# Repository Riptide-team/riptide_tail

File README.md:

# Compilation

## Arduino makefile

To compile and upload the code on the Arduino, [Arduino-Makefile](https://github.com/sudar/Arduino-Makefile) is used. Once installed, go to src, check that the arduino port is the port put in the Makefile at `MONITOR_PORT  = /dev/ttyUSB0`, and execute `make upload` 

# Serial communication

## Baudrate

The baudrate is `115200` and the communication is operating over usb between arduino and Raspberry Pi.

## Commands from raspberry

### Command frame
Commands from raspberry are sent using bytes. The line is finished by a `LF` (`\n`).

### Frame content
Bytes are hex values between 1000 and 2000 (coded on two consecutive bytes) which are direct us request on the output channel.
Channel order is :

- Thruster channel
- D fin channel
- P fin channel
- S fin channel

### Example

All to neutral:

`\0x05\0xDC\0x05\0xDC\0x05\0xDC\0x05\0xDC\0x0A`

Thruster full forward, fins full backward:

`\0x07\0xD0\0x03\0xE8\0x03\0xE8\0x53\0xE8\0x0A`

## Commands from arduino

### Command frame
Commands from raspberry are sent using bytes. The line is finished by a `LF` (`\n`).

### Frame content
Bytes are hex values between 1000 and 2000 (on three hexadecimal digits) which are direct us request from the RC captured by arduino and real generated PWM to actuators.
Channel order is :

- Thruster channel
- D fin channel
- P fin channel
- S fin channel
- RC channel 1 (Manual button)
- RC channel 2 (Timer button)
- RC channel 3 (Thruster)
- RC channel 4 (D fin)
- RC channel 5 (P fin)
- RC channel 6 (S fin)

### Example

All to neutral:

`\0x05\0xDC\0x05\0xDC\0x05\0xDC\0x05\0xDC\0x05\0xDC\0x05\0xDC\0x05\0xDC\0x05\0xDC\0x05\0xDC\0x05\0xDC\0x0A`

Thruster full forward, fins full backward, in manual mode, with timer at the minimum, so the RC captured commands are commands applied to the actuators:

`\0x07\0xD0\0x03\0xE8\0x03\0xE8\0x53\0xE8\0x07\0xD0\0x03\0xE8\0x07\0xD0\0x03\0xE8\0x03\0xE8\0x53\0xE8\0x0A`

## Picocom serial debug

To debug the serial communication, picocom can be used with the following configuration to correctly print hex characters:

```bash
picocom --imap spchex,nrmhex,8bithex,lfcrlf /dev/ttyUSB0 -b 115200
```

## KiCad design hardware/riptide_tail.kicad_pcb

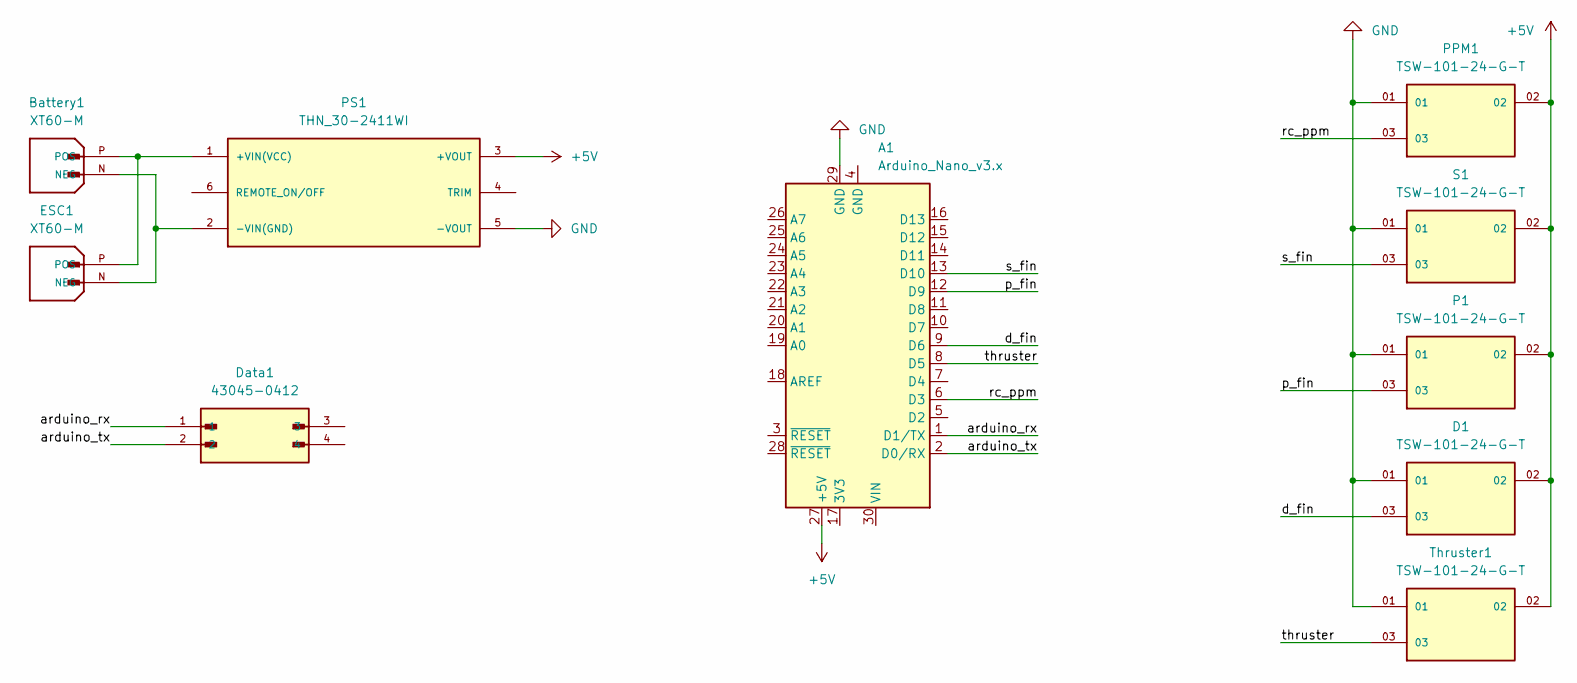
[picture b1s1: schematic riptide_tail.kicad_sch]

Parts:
A1: Arduino_Nano_v3.x; Arduino_Nano
Battery1: XT60-M; AMASS_XT60-M; PARTREV V1.2
D1: TSW-101-24-G-T; SAMTEC_TSW-101-24-G-T; PARTREV R
Data1: 43045-0412; MOLEX_43045-0412; PARTREV G1
ESC1: XT60-M; AMASS_XT60-M; PARTREV V1.2
P1: TSW-101-24-G-T; SAMTEC_TSW-101-24-G-T; PARTREV R
PPM1: TSW-101-24-G-T; SAMTEC_TSW-101-24-G-T; PARTREV R
PS1: THN_30-2411WI; CONV_THN_30-2411WI; PARTREV March 16, 2021
S1: TSW-101-24-G-T; SAMTEC_TSW-101-24-G-T; PARTREV R
Thruster1: TSW-101-24-G-T; SAMTEC_TSW-101-24-G-T; PARTREV R

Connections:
+5V: A1.27 (+5V), D1.02, P1.02, PPM1.02, PS1.3 (+VOUT), S1.02, Thruster1.02
/arduino_rx: A1.1 (D1/TX), Data1.1
/arduino_tx: A1.2 (D0/RX), Data1.2
/d_fin: A1.9 (D6), D1.03
/p_fin: A1.12 (D9), P1.03
/rc_ppm: A1.6 (D3), PPM1.03
/s_fin: A1.13 (D10), S1.03
/thruster: A1.8 (D5), Thruster1.03
GND: A1.29 (GND), D1.01, P1.01, PPM1.01, PS1.5 (-VOUT), S1.01, Thruster1.01
unnamed: Battery1.N (NEG), ESC1.N (NEG), PS1.2 (-VIN(GND))
unnamed: Battery1.P (POS), ESC1.P (POS), PS1.1 (+VIN(VCC))

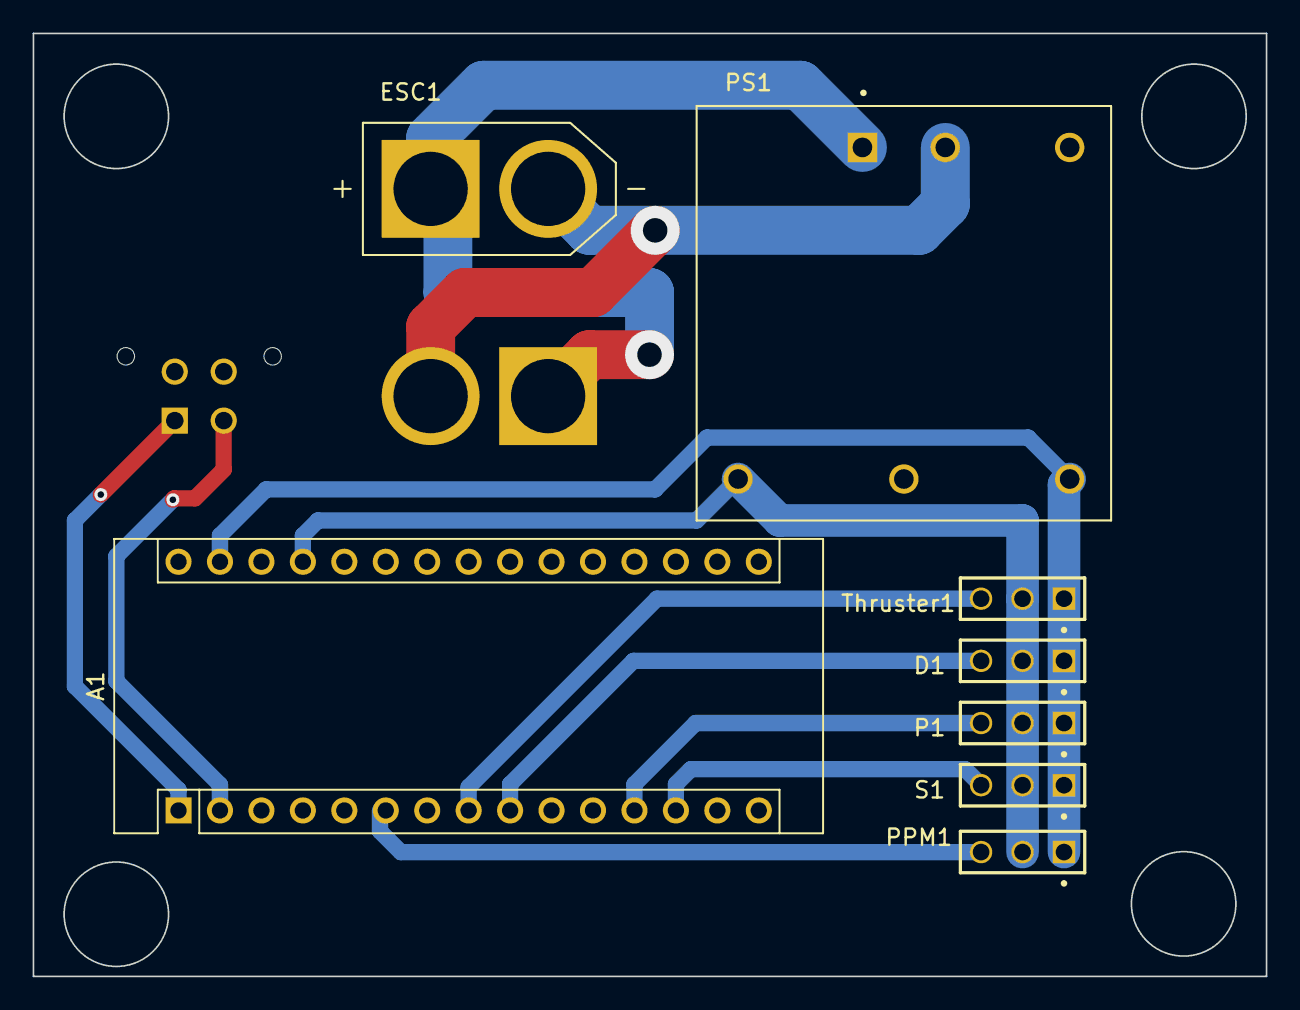
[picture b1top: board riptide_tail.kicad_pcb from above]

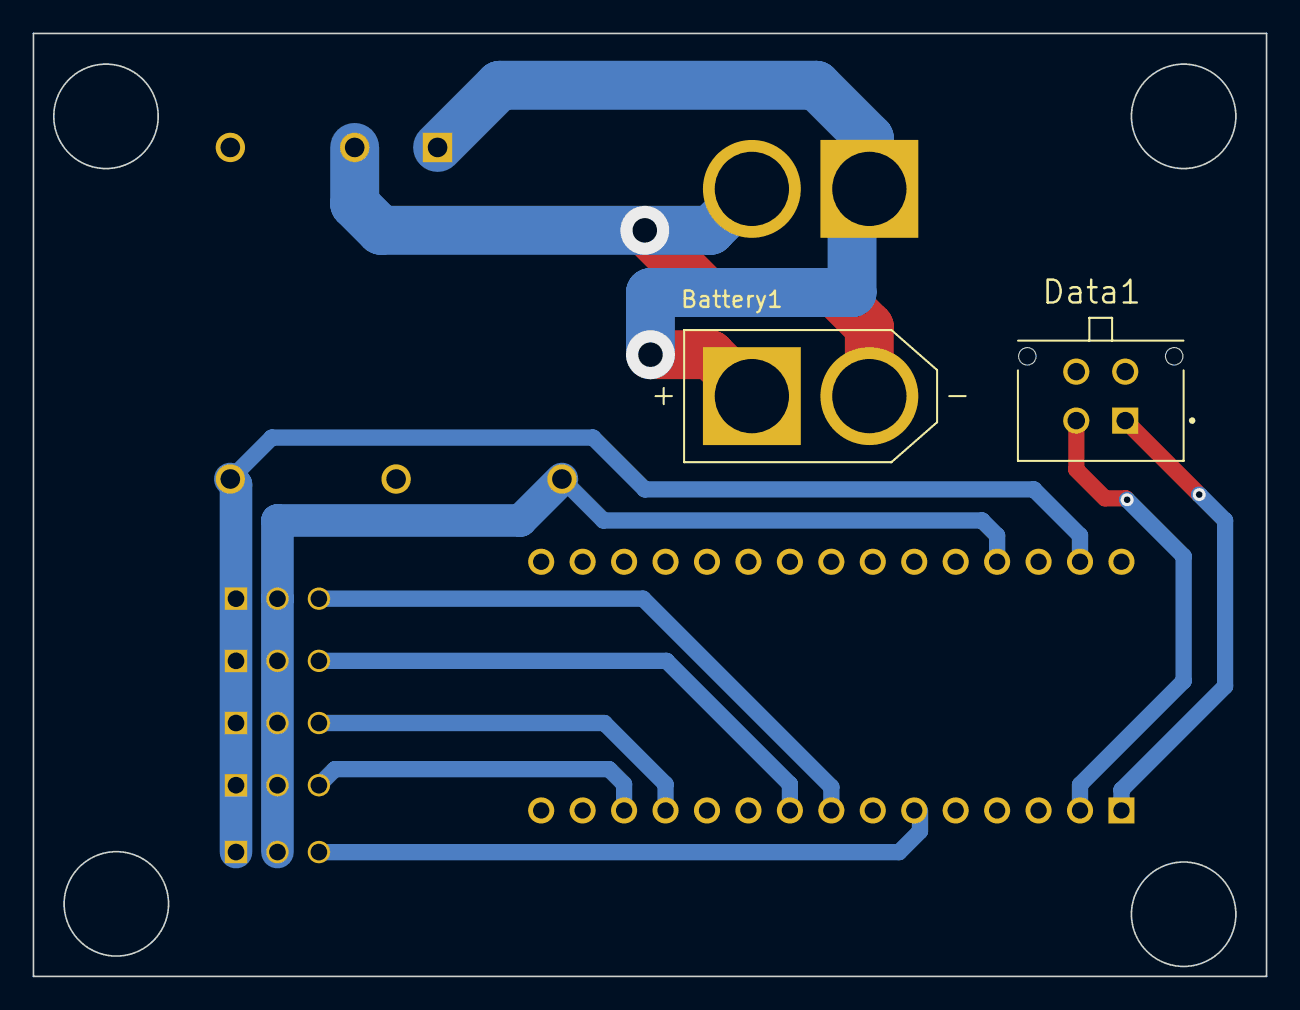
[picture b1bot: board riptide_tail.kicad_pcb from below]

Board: 2 copper layers, 75.6 x 57.8 mm, 10 parts (2 on the bottom side), 11 nets.

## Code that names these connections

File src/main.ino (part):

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PPMReader ppm(RC_PIN, CHANNEL_AMOUNT);

// Initialize actuators outputs
#define THRUSTER_PIN 5      // D5
#define D_FIN_PIN 6         // D6
#define P_FIN_PIN 9         // D9
#define S_FIN_PIN 10        // D10

Servo thruster;
Servo d_fin;
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    parser.addHandler("RHACT", RHACT_handler);

    // Servo creation
    thruster.attach(THRUSTER_PIN);
    d_fin.attach(D_FIN_PIN);
    p_fin.attach(P_FIN_PIN);
    s_fin.attach(S_FIN_PIN);

    // PPM tuning
    ppm.minChannelValue = 1000;     // (us)
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
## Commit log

2023-03-07 Updating README.md
2023-03-07 Clearing the temporary buffer at each new read
2023-04-11 Adding cad
2023-04-11 Updating .gitignore
2023-04-13 Updating CAO&EDA
2023-04-13 Adding pvc color
2023-06-05 Updating arduino script
